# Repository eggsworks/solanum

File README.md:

# Solanum

Solanum is a 34-key diodeless split keyboard based around Pro Micro compatible MCU modules. It features support for both wired and wireless builds and has been designed to be easily hand-assembled. The PCB is reversible and hotswap with support for Kailh Choc (v1) switches. 

## Features

The layout of Solanum differs from the typical 34-key split in that it has only one thumb key, and a reachy pinky key. Nominal key spacing is 19x18mm. All columns features a slight splay; the pinky columns are splayed more aggressively.

The top face of the switchplate (i.e., the face which is visible on the left hand side of the keyboard) features a botanical illustration of *Solanum melongena*, the eggplant.

Solanum includes support for a splitkb.com tenting puck

It features a TRRS port for wired builds, and
a dedicated battery JST and power switch for wireless builds.

## BOM

- 2x PCB
- 2x switchplate
- 2x Pro Micro compatible MCU module
- 34x Kailh Choc hotswap sockets
- 34x Kailh Choc switches
- 34x 1u Choc keycaps
- 12x nylon M2 screws
- 12x nylon 1mm M2 washers
- 12x nylon M2 nuts

For wired build:
- 2x PJ-320A TRRS jack
- 1x TRRS cable

For wireless build:
- 2x JST S2B-PH-K-S
- 2x C&K OS102011MA1QN1

Optional:
- 2x splitkb tenting pucks
- 2x 3D printed MCU cover (from [extras/](extras/))
- 4x 6mm M2 standoffs

## Build guide

[https://docs.eggs.works/docs/build-guides/solanum/](https://docs.eggs.works/docs/build-guides/solanum/)

## Firmware

ZMK: https://github.com/eggsworks/zmk-config/

QMK: https://github.com/eggsworks/qmk_firmware/tree/solanum/keyboards/eggsworks/solanum

## License

Solanum is provided under the terms of the [GPL v3](LICENSE). The following portions are derived from other projects:

- Choc, Pro Micro, TRRS, and jumpers used on the JST footprint: [keyboard_reversible.pretty](https://github.com/50an6xy06r6n/keyboard_reversible.pretty) by 50an6xy06r6n (MIT License)
- Tenting puck: [tenting_puck](https://github.com/splitkb/tenting_puck) by splitkb.com (MIT License)
- JST, SPDT, and mounting holes: [KiCad footprint library](https://kicad.github.io/footprints/) (CC BY-SA 4.0)

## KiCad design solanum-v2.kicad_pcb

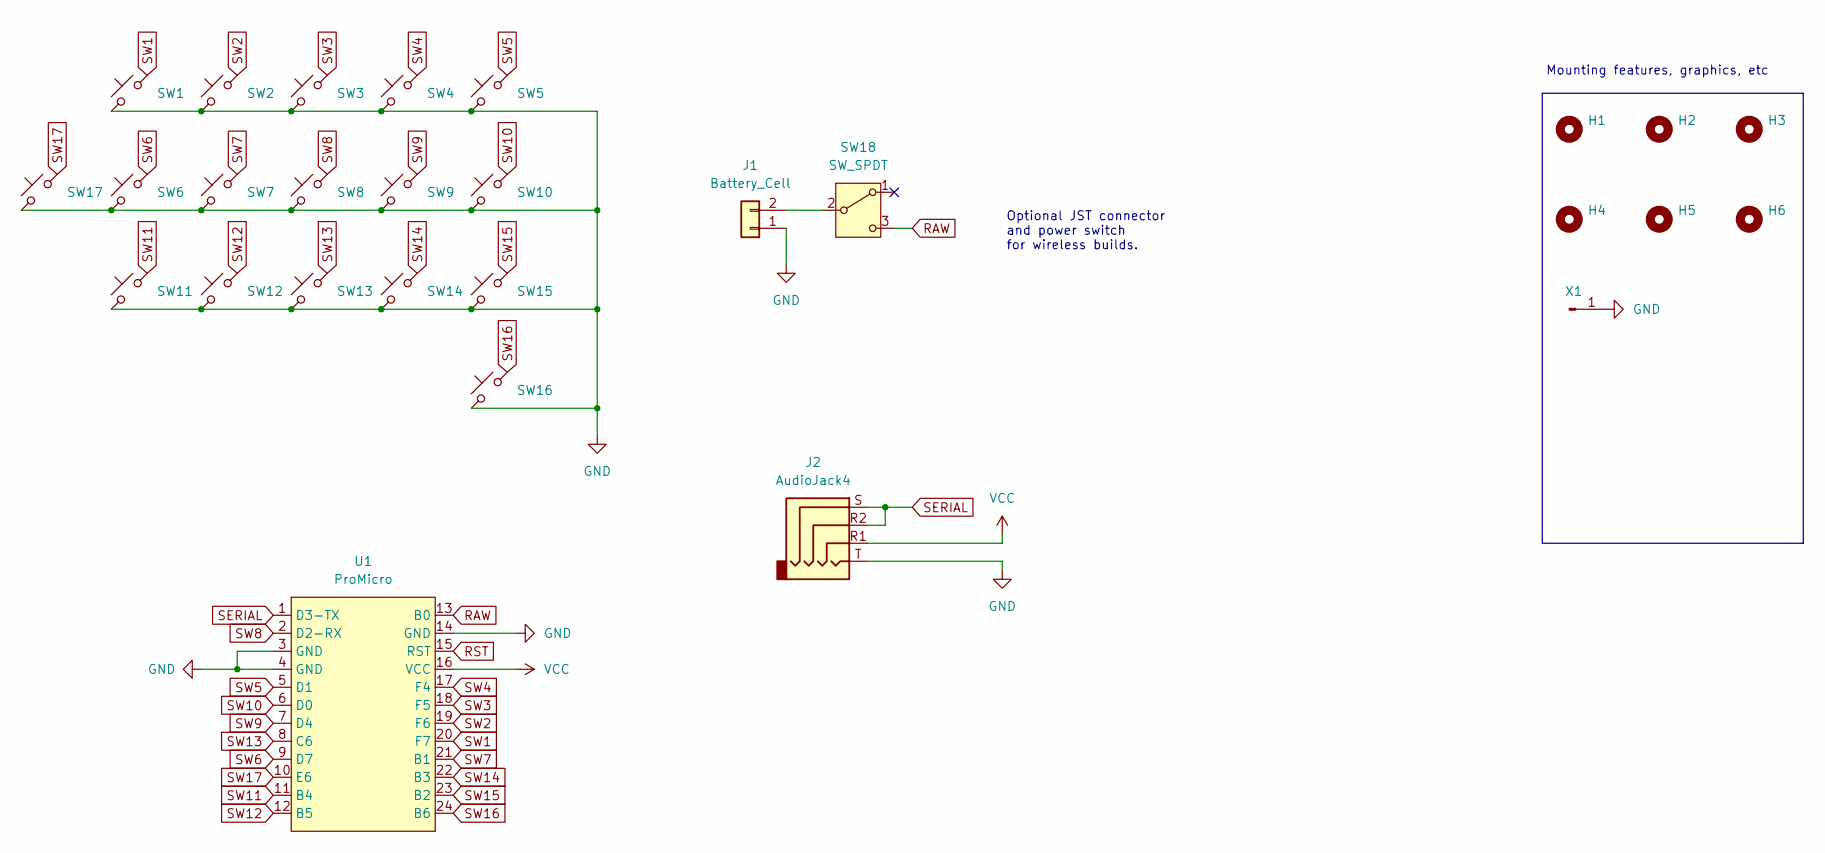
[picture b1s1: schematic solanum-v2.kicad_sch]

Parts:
H1, H2, H3, H4, H5, H6: MountingHole; MountingHole_2.2mm_M2
J1: Battery_Cell; JST_PH_S2B-PH-K_1x02_P2.00mm_Horizontal
J2: AudioJack4; PJ-320A
SW1, SW2, SW3, SW4, SW5, SW6, SW7, SW8, SW9, SW10, SW11, SW12, SW13, SW14, SW15, SW16, SW17: SW_Push_45deg; Choc_Hotswap
SW18: SW_SPDT; SW_SPDT_Shouhan_MSK12C02
U1: ProMicro
X1: Tenting puck; TentingPuck_NoHole

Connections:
GND: J1.1, J2.T, SW1.1, SW2.1, SW3.1, SW4.1, SW5.1, SW6.1, SW7.1, SW8.1, SW9.1, SW10.1, SW11.1, SW12.1, SW13.1, SW14.1, SW15.1, SW16.1, SW17.1, U1.3 (GND), U1.4 (GND), U1.14 (GND), X1.1
unnamed: J1.2, SW18.2 (B)
RAW: SW18.3 (C), U1.13 (B0)
RST: U1.15 (RST)
SERIAL: J2.R2, J2.S, U1.1 (D3-TX)
SW1: SW1.2, U1.20 (F7)
SW2: SW2.2, U1.19 (F6)
SW3: SW3.2, U1.18 (F5)
SW4: SW4.2, U1.17 (F4)
SW5: SW5.2, U1.5 (D1)
SW6: SW6.2, U1.9 (D7)
SW7: SW7.2, U1.21 (B1)
SW8: SW8.2, U1.2 (D2-RX)
SW9: SW9.2, U1.7 (D4)
SW10: SW10.2, U1.6 (D0)
SW11: SW11.2, U1.11 (B4)
SW12: SW12.2, U1.12 (B5)
SW13: SW13.2, U1.8 (C6)
SW14: SW14.2, U1.22 (B3)
SW15: SW15.2, U1.23 (B2)
SW16: SW16.2, U1.24 (B6)
SW17: SW17.2, U1.10 (E6)
VCC: J2.R1, U1.16 (VCC)

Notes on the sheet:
Optional JST connector and power switch for wireless builds.
Mounting features, graphics, etc

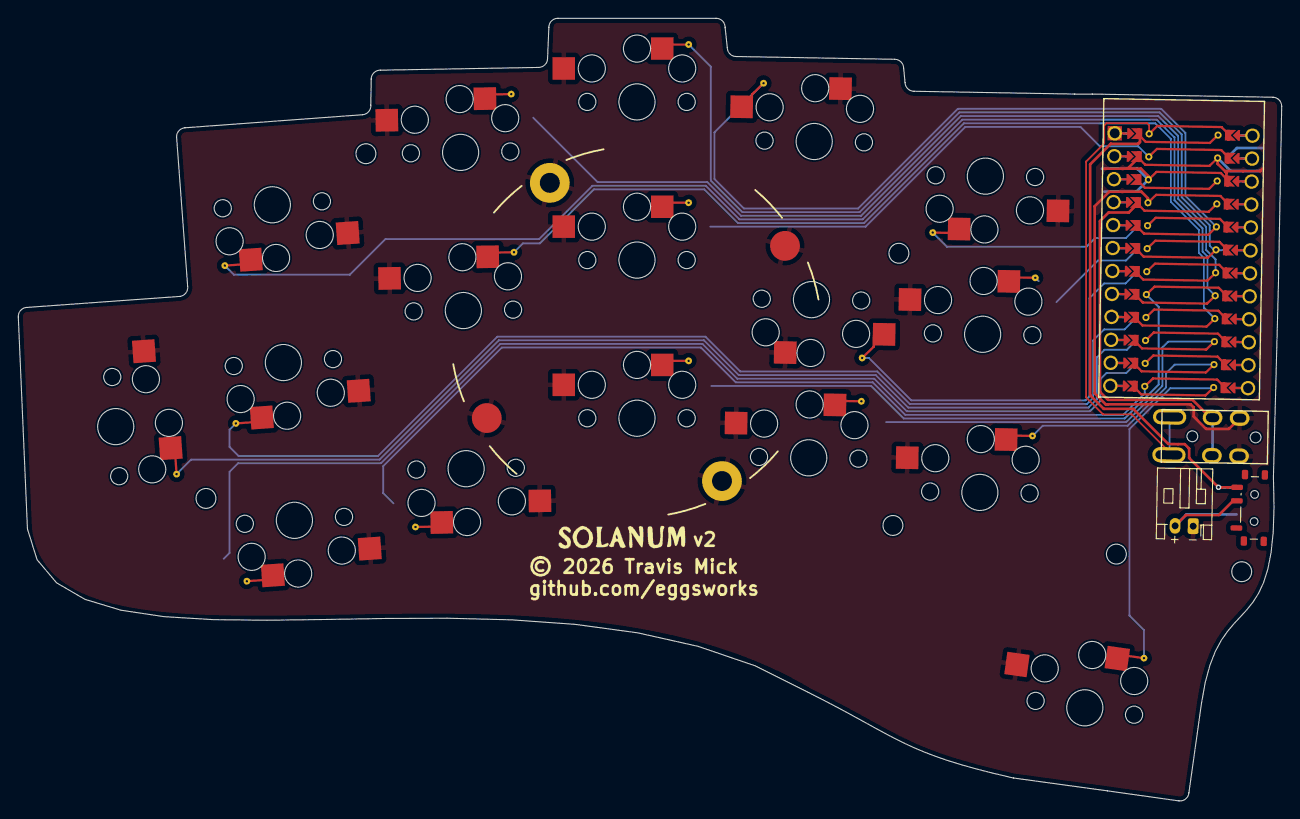
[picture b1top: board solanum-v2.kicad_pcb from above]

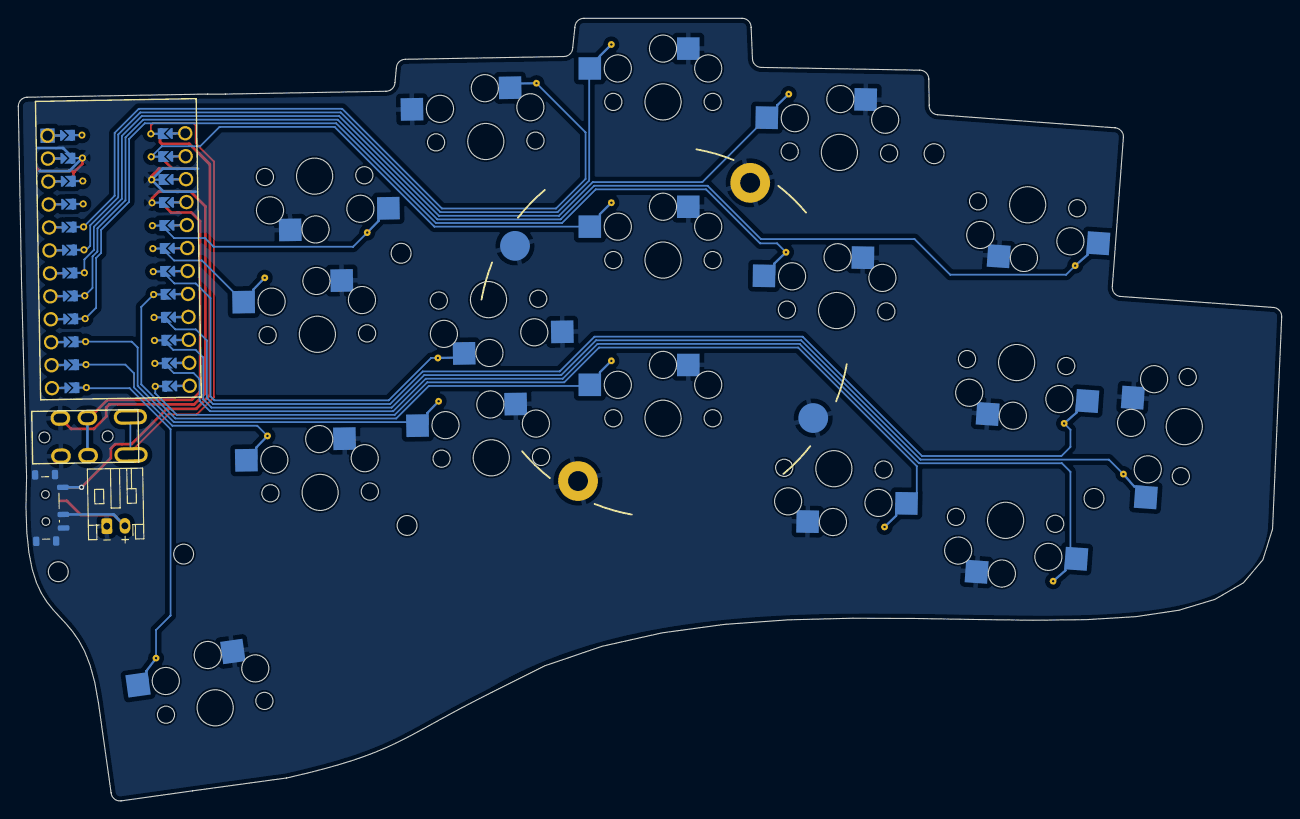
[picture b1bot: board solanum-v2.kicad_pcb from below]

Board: 2 copper layers, 139.8 x 86.6 mm, 28 parts (3 on the bottom side), 22 nets.

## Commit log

2024-09-20 Add MCU cover, update readme
2024-09-20 Add photo
2024-09-20 Add extra photos
2026-01-04 Rename files
2026-01-04 Updated ergogen
2026-01-05 progress on v2 pcb
2026-01-05 fine tuning
2026-01-05 fixup switch footprint

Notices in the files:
solanum-v2.kicad_pcb:
© 2026 Travis Mick
